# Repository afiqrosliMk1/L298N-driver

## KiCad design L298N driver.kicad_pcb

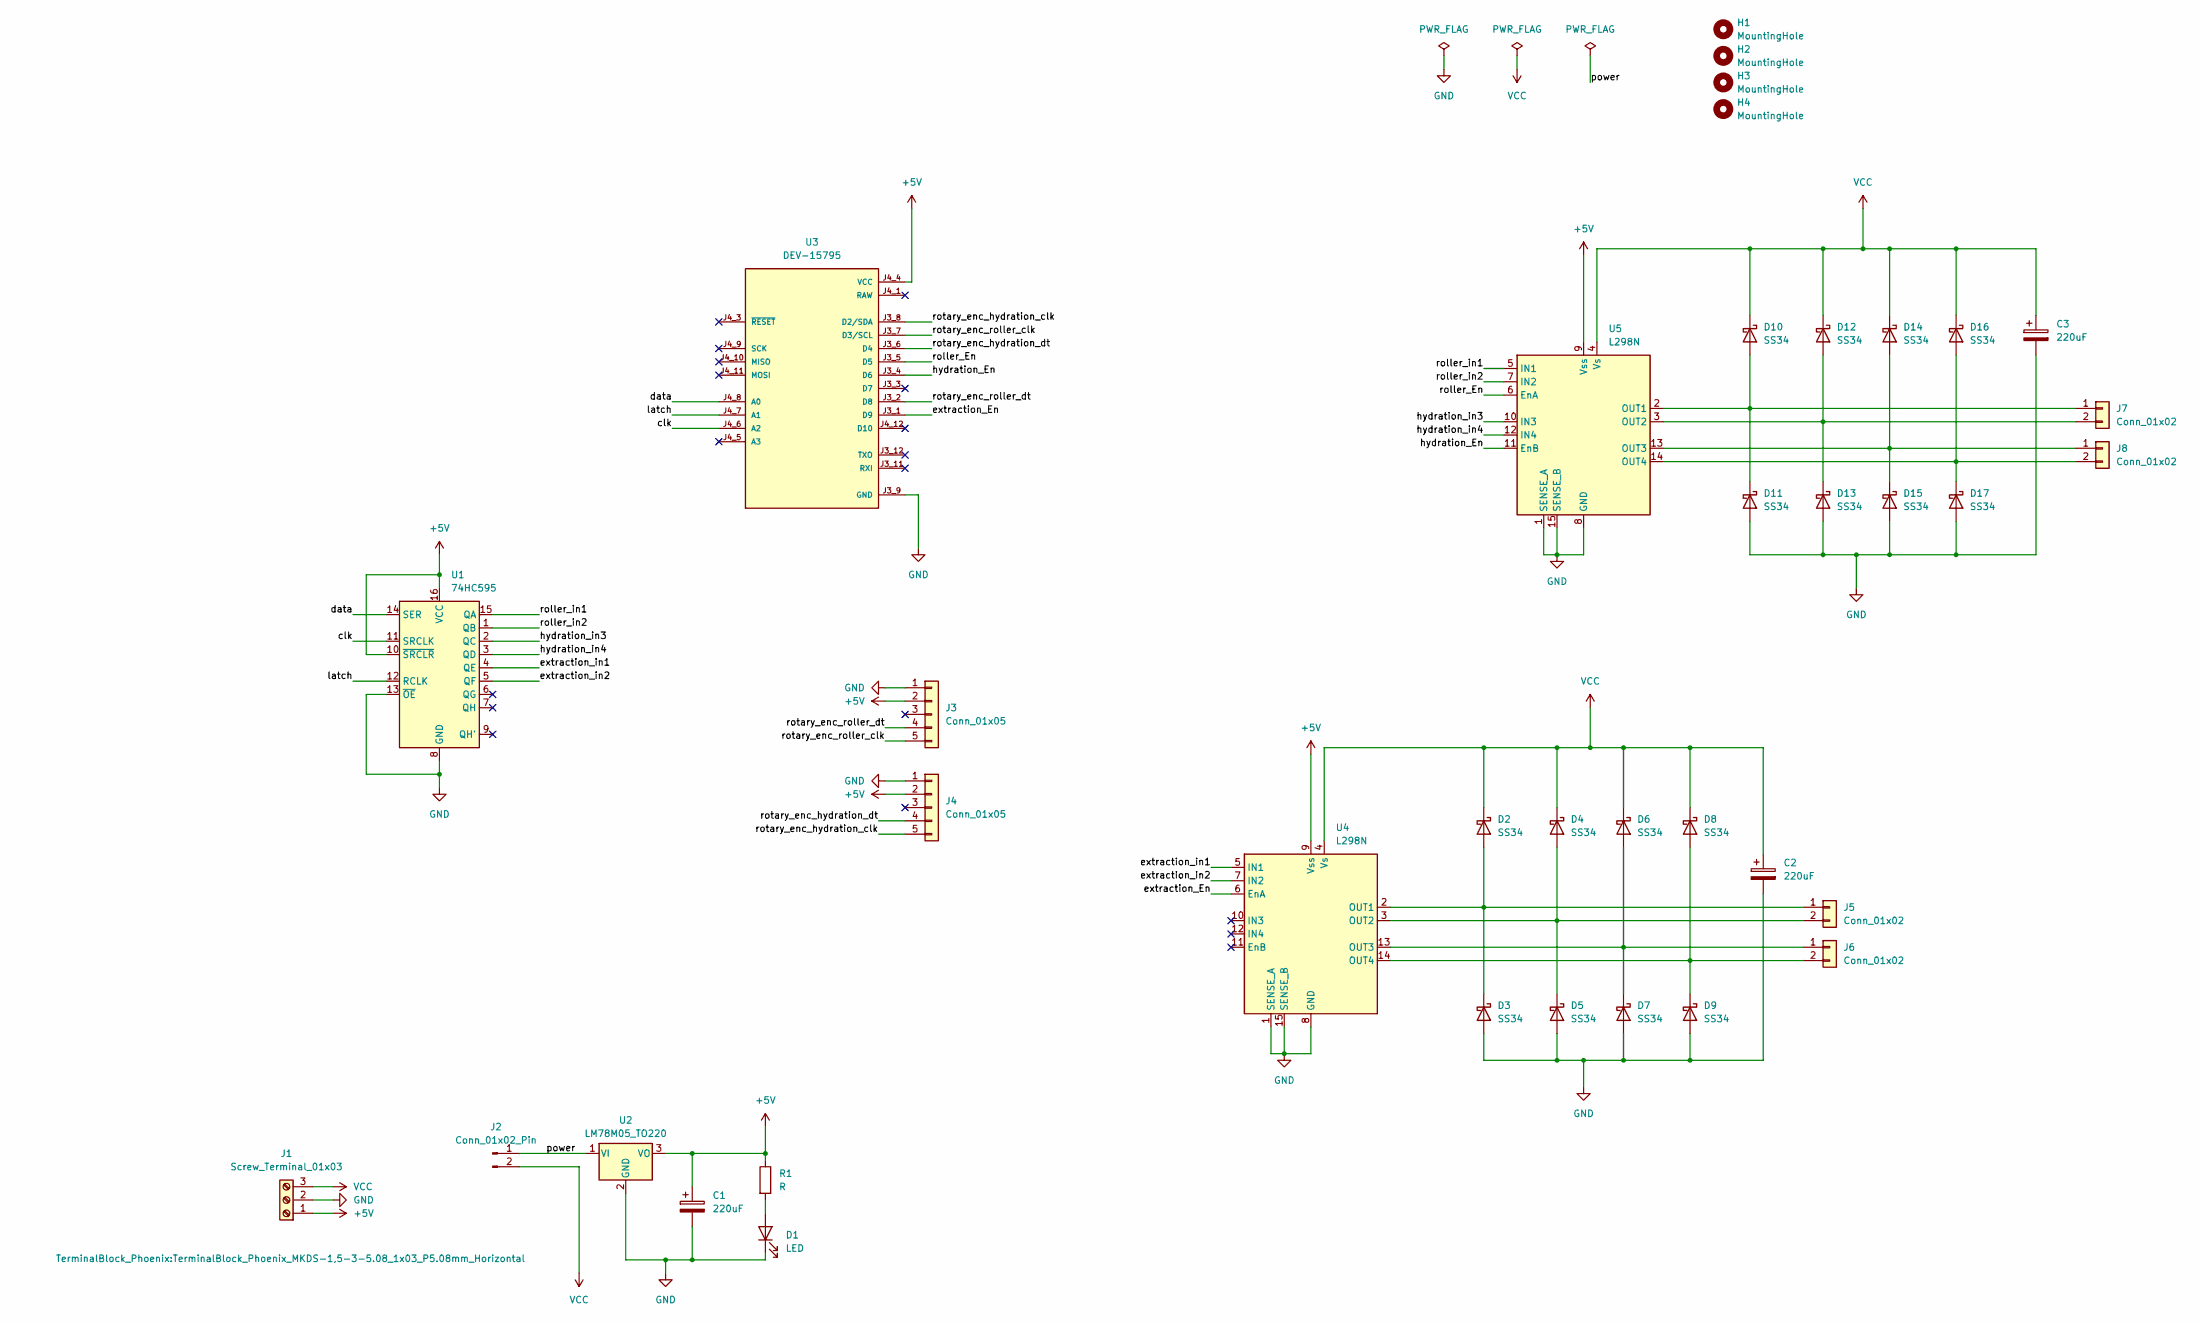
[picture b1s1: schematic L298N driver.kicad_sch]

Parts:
C1, C2, C3: 220uF; CP_Elec_8x10
D1: LED; LED_0805_2012Metric
D2, D3, D4, D5, D6, D7, D8, D9, D10, D11, D12, D13, D14, D15, D16, D17: SS34; D_SMA; PARTREV N/A
H1, H2, H3, H4: MountingHole; MountingHole_3.2mm_M3_Pad_Via
J1: Screw_Terminal_01x03; TerminalBlock_Phoenix_MKDS-1,5-3-5.08_1x03_P5.08mm_Horizont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
J2: Conn_01x02_Pin; PinHeader_1x02_P2.54mm_Vertical
J3, J4: Conn_01x05; JST_XH_B5B-XH-A_1x05_P2.50mm_Vertical
J5, J6, J7, J8: Conn_01x02; JST_XH_B2B-XH-A_1x02_P2.50mm_Vertical
R1: R; R_0805_2012Metric
U1: 74HC595; DIP-16_W7.62mm_Socket
U2: LM78M05_TO220; TO-220-3_Horizontal_TabDown
U3: DEV-15795; MODULE_DEV-15795; PARTREV 2.0
U4, U5: L298N; TO-220-15_P2.54x5.08mm_StaggerOdd_Lead4.58mm_Vertical

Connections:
+5V: C1.1, J1.1, J3.2, J4.2, R1.1, U1.10 (~SRCLR), U1.16 (VCC), U2.3 (VO), U3.J4_4 (VCC), U4.9 (Vss), U5.9 (Vss)
/clk: U1.11 (SRCLK), U3.J4_6 (A2)
/data: U1.14 (SER), U3.J4_8 (A0)
/extraction_En: U3.J3_1 (D9), U4.6 (EnA)
/extraction_in1: U1.4 (QE), U4.5 (IN1)
/extraction_in2: U1.5 (QF), U4.7 (IN2)
/hydration_En: U3.J3_4 (D6), U5.11 (EnB)
/hydration_in3: U1.2 (QC), U5.10 (IN3)
/hydration_in4: U1.3 (QD), U5.12 (IN4)
/latch: U1.12 (RCLK), U3.J4_7 (A1)
/power: J2.1, U2.1 (VI)
/roller_En: U3.J3_5 (D5), U5.6 (EnA)
/roller_in1: U1.15 (QA), U5.5 (IN1)
/roller_in2: U1.1 (QB), U5.7 (IN2)
/rotary_enc_hydration_clk: J4.5, U3.J3_8 (D2/SDA)
/rotary_enc_hydration_dt: J4.4, U3.J3_6 (D4)
/rotary_enc_roller_clk: J3.5, U3.J3_7 (D3/SCL)
/rotary_enc_roller_dt: J3.4, U3.J3_2 (D8)
GND: C1.2, C2.2, C3.2, D1.1 (K), D3.2 (A), D5.2 (A), D7.2 (A), D9.2 (A), D11.2 (A), D13.2 (A), D15.2 (A), D17.2 (A), J1.2, J3.1, J4.1, U1.8 (GND), U1.13 (~OE), U2.2 (GND), U3.J3_9 (GND), U3.J3_10 (GND), U3.J4_2 (GND), U4.1 (SENSE_A), U4.8 (GND), U4.15 (SENSE_B), U5.1 (SENSE_A), U5.8 (GND), U5.15 (SENSE_B)
unnamed: D1.2 (A), R1.2
unnamed: D2.2 (A), D3.1 (K), J5.1, U4.2 (OUT1)
unnamed: D4.2 (A), D5.1 (K), J5.2, U4.3 (OUT2)
unnamed: D6.2 (A), D7.1 (K), J6.1, U4.13 (OUT3)
unnamed: D8.2 (A), D9.1 (K), J6.2, U4.14 (OUT4)
unnamed: D10.2 (A), D11.1 (K), J7.1, U5.2 (OUT1)
unnamed: D12.2 (A), D13.1 (K), J7.2, U5.3 (OUT2)
unnamed: D14.2 (A), D15.1 (K), J8.1, U5.13 (OUT3)
unnamed: D16.2 (A), D17.1 (K), J8.2, U5.14 (OUT4)
VCC: C2.1, C3.1, D2.1 (K), D4.1 (K), D6.1 (K), D8.1 (K), D10.1 (K), D12.1 (K), D14.1 (K), D16.1 (K), J1.3, J2.2, U4.4 (Vs), U5.4 (Vs)

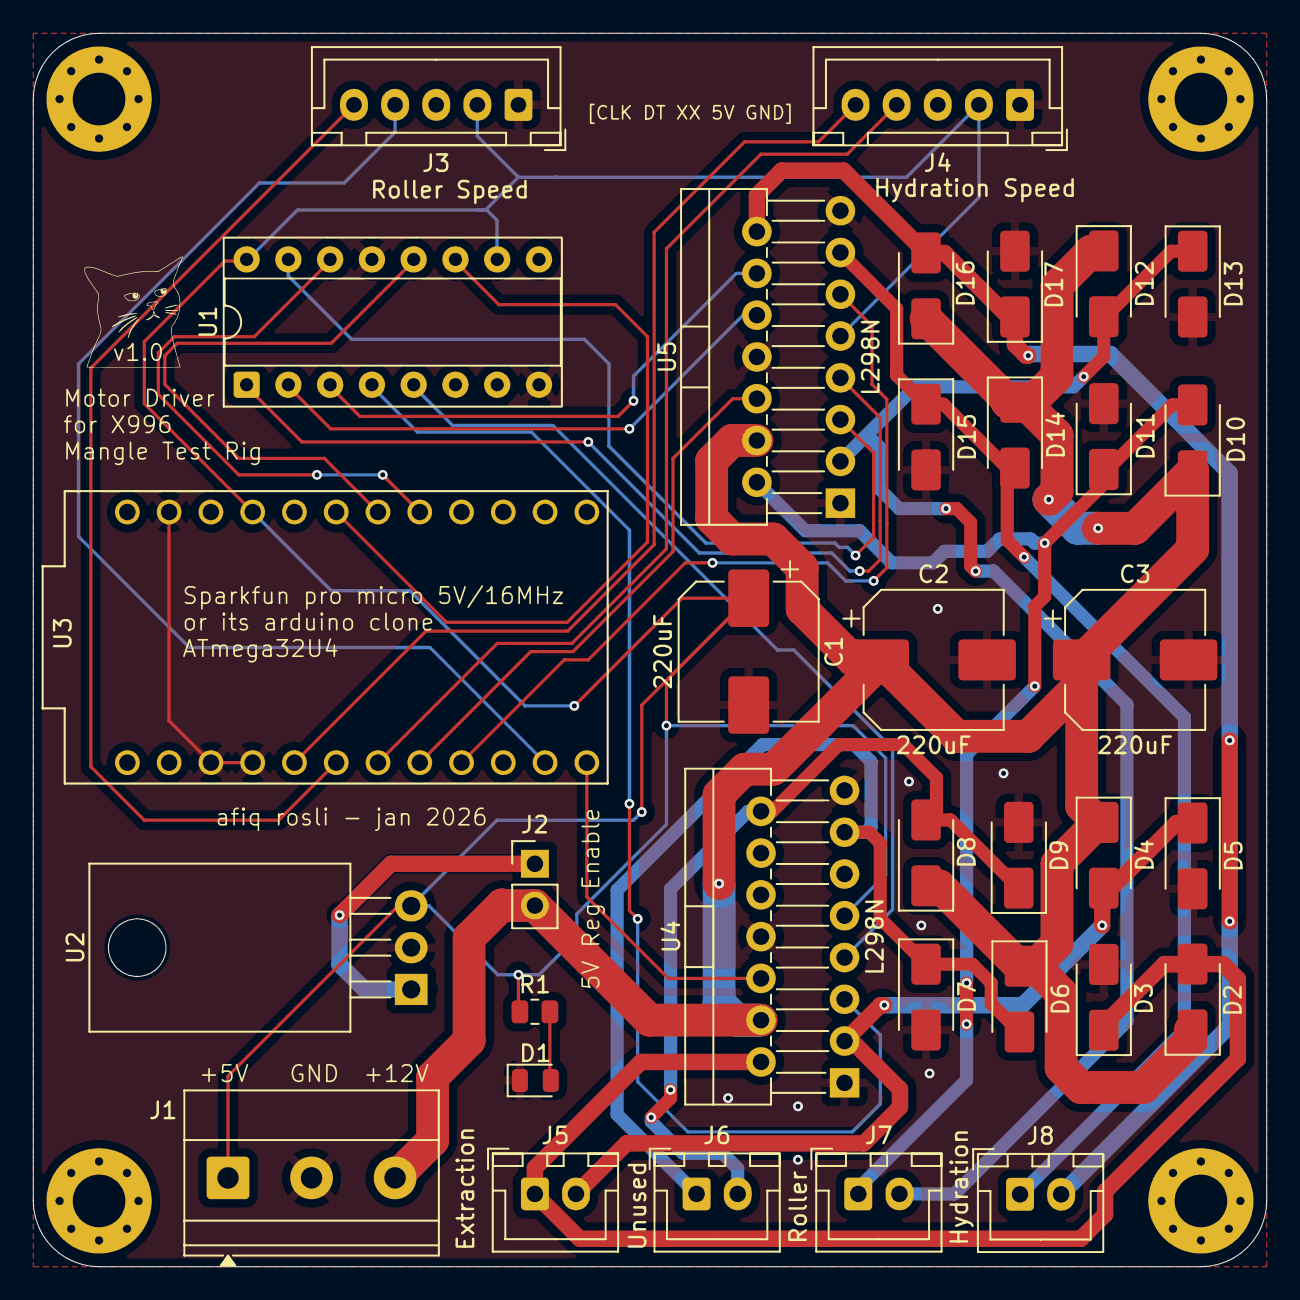
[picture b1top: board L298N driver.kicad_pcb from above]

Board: 2 copper layers, 75.0 x 75.0 mm, 38 parts (0 on the bottom side), 29 nets.

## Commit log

2026-01-20 first draft
2026-01-20 add README
2026-01-21 changed to fast switching diode UF4004
2026-01-22 preliminary component placement and trace routing
2026-01-25 finished preliminary routing
2026-01-26 rounded corners
2026-01-26 fat traces for 12v and L298N out
2026-01-26 silkscreen labels
2026-01-26 png for README
2026-01-26 add preview pic to the README
2026-01-26 copper pour
2026-01-27 initial component layout and smd diode
2026-01-28 draft layout for smd and 3x3 board. drc error still exist
2026-01-28 fix silkscreen and thermal relief issue
2026-01-28 update silkscreen zoning out cat
2026-01-29 fat VCC traces
2026-01-29 fat OUT traces
2026-01-31 update gitignore and add gerbers folder
2026-01-31 gitignore everything in gerbers except gitkeep
2026-01-31 fine tune traces
2026-02-03 update preview photo
2026-03-07 correct shift register to DIP-16 and power net trace width
